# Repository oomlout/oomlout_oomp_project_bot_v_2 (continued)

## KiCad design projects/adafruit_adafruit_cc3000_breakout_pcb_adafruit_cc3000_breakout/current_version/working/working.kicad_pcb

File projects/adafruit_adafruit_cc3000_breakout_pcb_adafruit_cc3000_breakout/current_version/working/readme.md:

# adafruit_cc3000_breakout_pcb
 
## summary 
* id: adafruit_adafruit_cc3000_breakout_pcb_adafruit_cc3000_breakout
* user: adafruit
* name: adafruit_cc3000_breakout_pcb
* board: adafruit_cc3000_breakout
* repo: https://github.com/adafruit/Adafruit-CC3000-Breakout-PCB

* src_file_repo_sch: 
* src_file_repo_sch_link: https://github.com/adafruit/Adafruit-CC3000-Breakout-PCB/tree/master/
* full details link: https://github.com/oomlout/oomlout_oomp_project_bot_v_2/tree/main/projects/adafruit_adafruit_cc3000_breakout_pcb_adafruit_cc3000_breakout/current_version/working  

## schematic  
  
[schematic (pdf)](working_schematic.pdf) 

## pcb  

[board (pdf)](working.pdf)  

## working_bom
| Id | Designator | Footprint | Quantity | Designation | Supplier and ref |  | None | 
| --- | --- | --- | --- | --- | --- | --- | --- | 
| 1 | X1 | ANT_2500AT44M0400 | 1 | 2500AT44M0400E |  |  | [''] | 
| 2 | LED1 | CHIPLED_0805_NOOUTLINE | 1 | green |  |  | [''] | 
| 3 | L2 | _0402 | 1 | 2.2nH |  |  | [''] | 
| 4 | U3 | SOIC16 | 1 | 74HC4050D |  |  | [''] | 
| 5 | C7,C6,C8 | _0805MP | 3 | 10ÂµF |  |  | [''] | 
| 6 | U$34,U$24 | MOUNTINGHOLE_2.5_PLATED | 2 | MOUNTINGHOLE2.5 |  |  | [''] | 
| 7 | C3 | _0402 | 1 | DNC_10pF |  |  | [''] | 
| 8 | C5,C4 | _0805MP | 2 | 1ÂµF |  |  | [''] | 
| 9 | JP3 | 1X09_ROUND_70 | 1 |  |  |  | [''] | 
| 10 | U1 | CC3000MOD | 1 | CC3000MOD |  |  | [''] | 
| 11 | U$8 | ADAFRUIT_5MM | 1 |  |  |  | [''] | 
| 12 | C2 | _0402 | 1 | 10pF |  |  | [''] | 
| 13 | U2 | SOT223-R | 1 |  |  |  | [''] | 
| 14 | FB1 | _0805MP | 1 |  |  |  | [''] | 
| 15 | FID1,FID2,FID3 | FIDUCIAL_1MM | 3 | FIDUCIAL" |  |  | [''] | 
| 16 | R2,R3 | _0805MP | 2 | 10K |  |  | [''] | 
| 17 | U$35 | U.FL | 1 | U.FL |  |  | [''] | 
| 18 | L1 | _0402 | 1 | DNP |  |  | [''] | 
| 19 | C1 | _0402 | 1 | 2.2pF |  |  | [''] | 
| 20 | JP1 | 1X03_ROUND | 1 |  |  |  | [''] | 
| 21 | R1 | 0805-NO | 1 | 470 |  |  | [''] | 
| 22 | U$36 | ADAFRUIT_TEXT_20MM | 1 |  |  |  | [''] | 
| 23 | TP2 | TESTPOINT_PAD_1MM | 1 | SDA |  |  | [''] | 
| 24 | SJ1 | SOLDERJUMPER_CLOSEDWIRE | 1 | TESTMODE |  |  | [''] | 
| 25 | TP1 | TESTPOINT_PAD_1MM | 1 | SCL |  |  | [''] | 

## bom_schematic
| Ref | Qnty | Value | Cmp name | Footprint | Description | Vendor | DNP | 
| --- | --- | --- | --- | --- | --- | --- | --- | 
| C1 | 1 | 2.2pF | CAP_CERAMIC_0402 | working:_0402 |  |  |  | 
| C2 | 1 | 10pF | CAP_CERAMIC_0402 | working:_0402 |  |  |  | 
| C3 | 1 | DNC_10pF | CAP_CERAMIC_0402 | working:_0402 |  |  |  | 
| C4, C5 | 2 | 1ÂµF | CAP_CERAMIC_0805MP | working:_0805MP |  |  |  | 
| C6, C7, C8 | 3 | 10ÂµF | CAP_CERAMIC_0805MP | working:_0805MP |  |  |  | 
| FB1 | 1 | FERRITE_0805MP | FERRITE_0805MP | working:_0805MP |  |  |  | 
| FID1, FID2, FID3 | 3 | FIDUCIAL"" | FIDUCIAL{dblquote}{dblquote} | working:FIDUCIAL_1MM |  |  |  | 
| JP1 | 1 | HEADER-1X3ROUND | HEADER-1X3ROUND | working:1X03_ROUND |  |  |  | 
| JP3 | 1 | HEADER-1X970MIL | HEADER-1X970MIL | working:1X09_ROUND_70 |  |  |  | 
| L1 | 1 | DNP | INDUCTOR_0402 | working:_0402 |  |  |  | 
| L2 | 1 | 2.2nH | INDUCTOR_0402 | working:_0402 |  |  |  | 
| LED1 | 1 | green | LED0805_NOOUTLINE | working:CHIPLED_0805_NOOUTLINE |  |  |  | 
| R1 | 1 | 470 | RESISTOR0805_NOOUTLINE | working:0805-NO |  |  |  | 
| R2, R3 | 2 | 10K | RESISTOR_0805MP | working:_0805MP |  |  |  | 
| SJ1 | 1 | TESTMODE | SOLDERJUMPER_CLOSED | working:SOLDERJUMPER_CLOSEDWIRE |  |  |  | 
| TP1 | 1 | SCL | TESTPOINTPAD1MM | working:TESTPOINT_PAD_1MM |  |  |  | 
| TP2 | 1 | SDA | TESTPOINTPAD1MM | working:TESTPOINT_PAD_1MM |  |  |  | 
| U1 | 1 | CC3000MOD | CC3000MOD | working:CC3000MOD |  |  |  | 
| U2 | 1 | VREG_SOT223 | VREG_SOT223 | working:SOT223-R |  |  |  | 
| U3 | 1 | 74HC4050D | 74HC4050D | working:SOIC16 |  |  |  | 
| U$24, U$34 | 2 | MOUNTINGHOLE2.5 | MOUNTINGHOLE2.5 | working:MOUNTINGHOLE_2.5_PLATED |  |  |  | 
| U$35 | 1 | U.FL | U.FL | working:U.FL |  |  |  | 
| X1 | 1 | 2500AT44M0400E | ANTENNA_JOHANSON_2500AT44M0400 | working:ANT_2500AT44M0400 |  |  |  | 

## mounting_holes
| x | y | package | value | ref | size | 
| --- | --- | --- | --- | --- | --- | 
| 0.0 | 0.0 | MOUNTINGHOLE_2.5_PLATED | MOUNTINGHOLE2.5 | U$24 | m3 | 
| 21.0 | 0.0 | MOUNTINGHOLE_2.5_PLATED | MOUNTINGHOLE2.5 | U$34 | m3 |

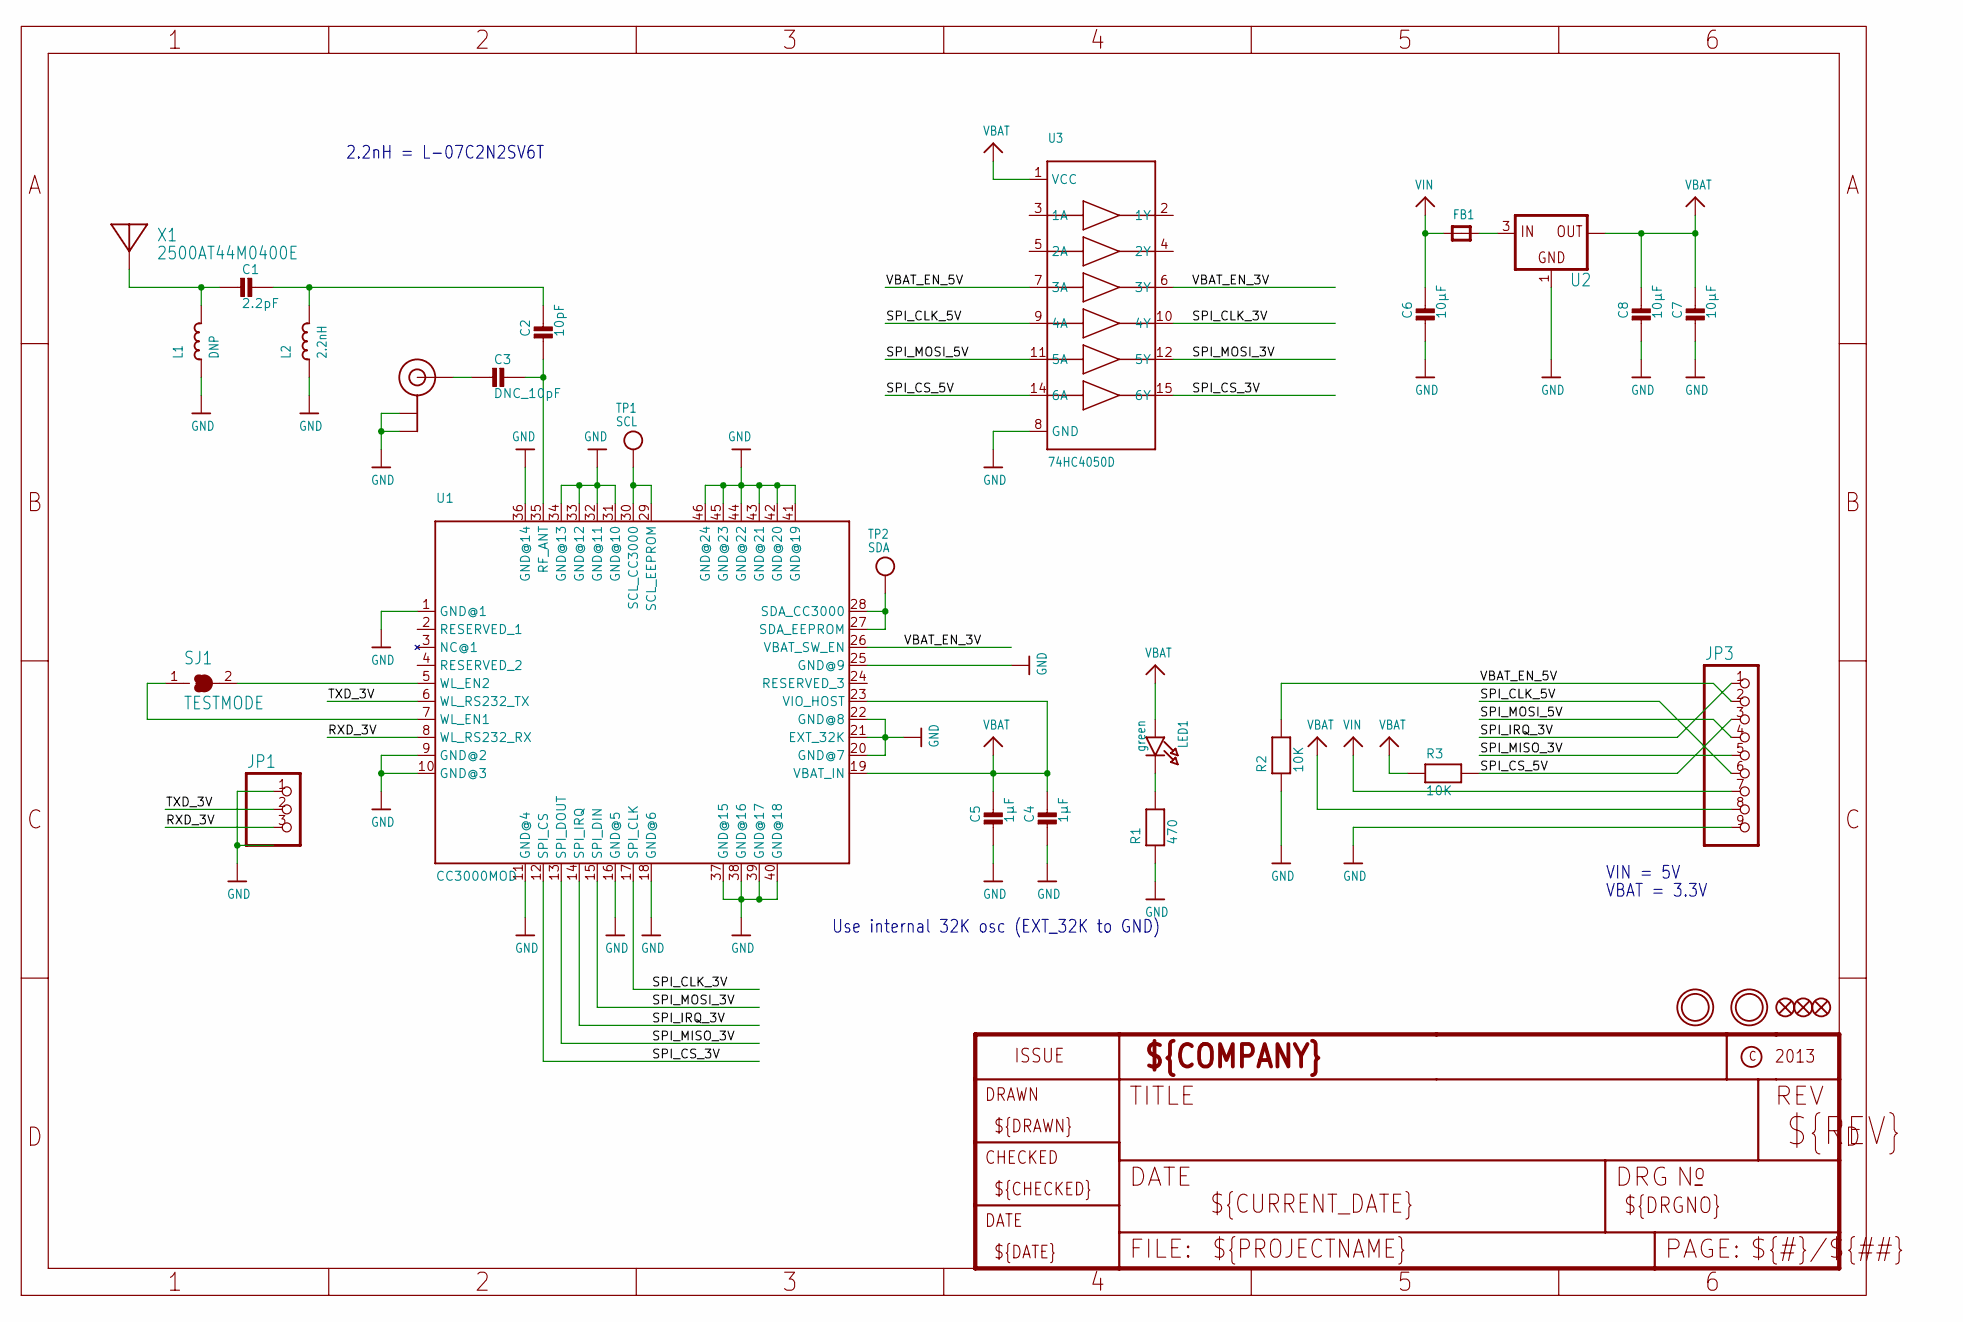
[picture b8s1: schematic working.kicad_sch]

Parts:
C1: 2.2pF; _0402
C2: 10pF; _0402
C3: DNC_10pF; _0402
C4, C5: 1µF; _0805MP
C6, C7, C8: 10µF; _0805MP
FB1: FERRITE_0805MP; _0805MP
FID1, FID2, FID3: FIDUCIAL""; FIDUCIAL_1MM
JP1: HEADER-1X3ROUND; 1X03_ROUND
JP3: HEADER-1X970MIL; 1X09_ROUND_70
L1: DNP; _0402
L2: 2.2nH; _0402
LED1: green; CHIPLED_0805_NOOUTLINE
R1: 470; 0805-NO
R2, R3: 10K; _0805MP
SJ1: TESTMODE; SOLDERJUMPER_CLOSEDWIRE
TP1: SCL; TESTPOINT_PAD_1MM
TP2: SDA; TESTPOINT_PAD_1MM
U1: CC3000MOD
U2: VREG_SOT223; SOT223-R
U3: 74HC4050D; SOIC16
U$24, U$34: MOUNTINGHOLE2.5; MOUNTINGHOLE_2.5_PLATED
U$35: U.FL
X1: 2500AT44M0400E; ANT_2500AT44M0400

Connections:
GND: C4.2, C5.2, C6.2, C7.2, C8.2, JP1.1, JP3.9, L1.1, L2.1, R1.1, R2.1, U1.1 (GND@1), U1.9 (GND@2), U1.10 (GND@3), U1.11 (GND@4), U1.16 (GND@5), U1.18 (GND@6), U1.20 (GND@7), U1.21 (EXT_32K), U1.22 (GND@8), U1.25 (GND@9), U1.31 (GND@10), U1.32 (GND@11), U1.33 (GND@12), U1.34 (GND@13), U1.36 (GND@14), U1.37 (GND@15), U1.38 (GND@16), U1.39 (GND@17), U1.40 (GND@18), U1.41 (GND@19), U1.42 (GND@20), U1.43 (GND@21), U1.44 (GND@22), U1.45 (GND@23), U1.46 (GND@24), U2.1 (GND), U3.8 (GND), U$35.P$1 (GND@0), U$35.P$2 (GND@1)
unnamed: C1.2, L1.2, X1.FEED
unnamed: C1.1, C2.1, L2.2
unnamed: C3.2, U$35.P$3 (SIGNAL)
unnamed: C2.2, C3.1, U1.35 (RF_ANT)
unnamed: SJ1.2, U1.5 (WL_EN2)
unnamed: SJ1.1, U1.7 (WL_EN1)
unnamed: LED1.C, R1.2
unnamed: FB1.2, U2.3 (IN)
RXD_3V: JP1.3, U1.8 (WL_RS232_RX)
SCL_3V: TP1.P$1, U1.29 (SCL_EEPROM), U1.30 (SCL_CC3000)
SDA_3V: TP2.P$1, U1.27 (SDA_EEPROM), U1.28 (SDA_CC3000)
SPI_CLK_3V: U1.17 (SPI_CLK), U3.10 (4Y)
SPI_CLK_5V: JP3.6, U3.9 (4A)
SPI_CS_3V: U1.12 (SPI_CS), U3.15 (6Y)
SPI_CS_5V: JP3.3, R3.2, U3.14 (6A)
SPI_IRQ_3V: JP3.1, U1.14 (SPI_IRQ)
SPI_MISO_3V: JP3.5, U1.13 (SPI_DOUT)
SPI_MOSI_3V: U1.15 (SPI_DIN), U3.12 (5Y)
SPI_MOSI_5V: JP3.4, U3.11 (5A)
TXD_3V: JP1.2, U1.6 (WL_RS232_TX)
VBAT: C4.1, C5.1, C7.1, C8.1, JP3.8, LED1.A, R3.1, U1.19 (VBAT_IN), U1.23 (VIO_HOST), U2.2 (OUT), U2.4 (OUT), U3.1 (VCC)
VBAT_EN_3V: U1.26 (VBAT_SW_EN), U3.6 (3Y)
VBAT_EN_5V: JP3.2, R2.2, U3.7 (3A)
VIN: C6.1, FB1.1, JP3.7

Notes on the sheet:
VIN = 5V
2.2nH = L-07C2N2SV6T
Use internal 32K osc (EXT_32K to GND)
VBAT = 3.3V

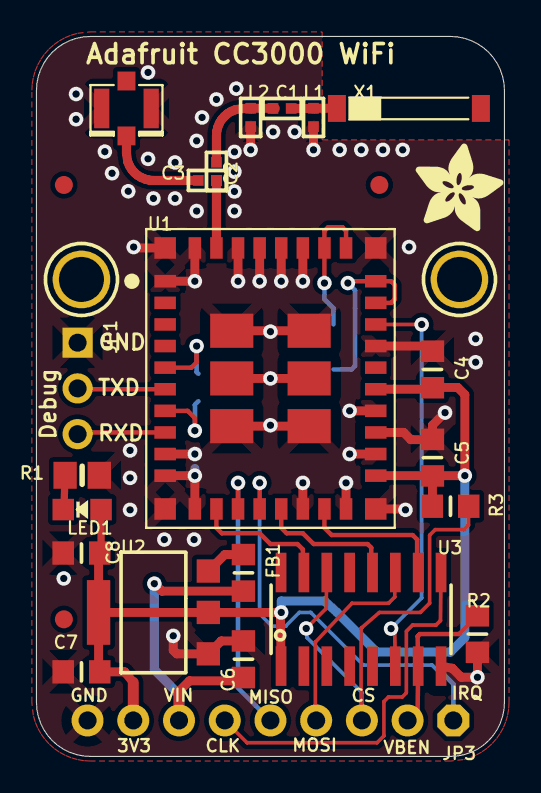
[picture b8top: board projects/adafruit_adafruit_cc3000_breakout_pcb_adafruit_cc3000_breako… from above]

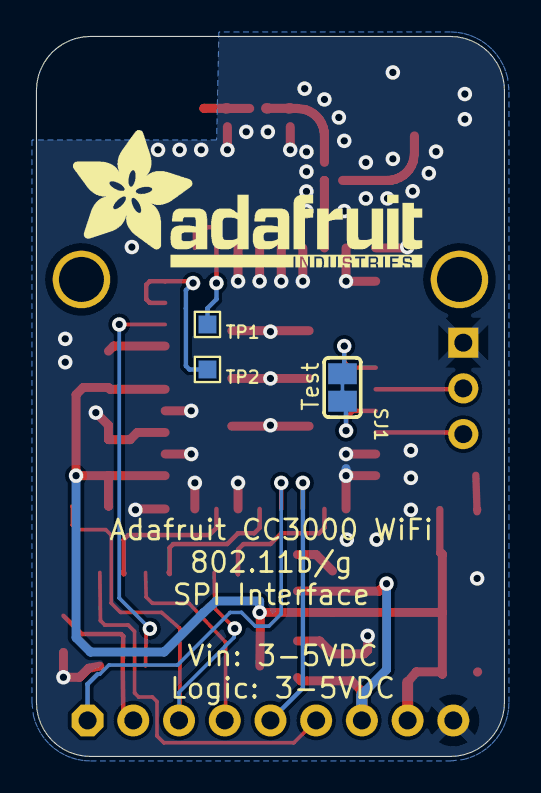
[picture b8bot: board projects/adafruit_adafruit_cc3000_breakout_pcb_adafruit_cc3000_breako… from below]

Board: 2 copper layers, 26.0 x 40.0 mm, 32 parts (4 on the bottom side), 25 nets.

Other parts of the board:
U$8: ADAFRUIT_5MM
U$36: ADAFRUIT_TEXT_20MM
